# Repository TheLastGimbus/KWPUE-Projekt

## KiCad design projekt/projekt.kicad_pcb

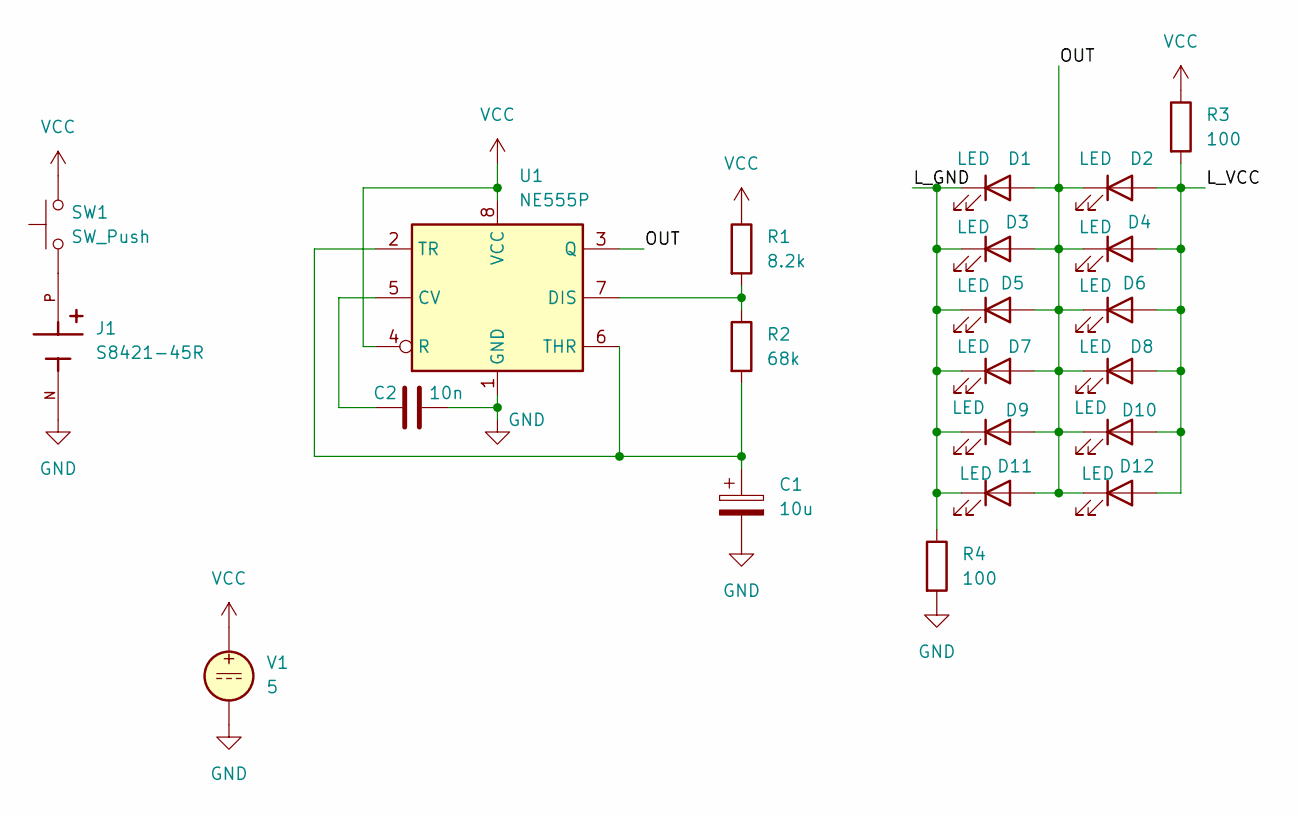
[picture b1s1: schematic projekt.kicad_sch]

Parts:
C1: 10u; CP_Radial_D4.0mm_P2.00mm
C2: 10n; C_Disc_D4.3mm_W1.9mm_P5.00mm
D1, D2, D3, D4, D5, D6, D7, D8, D9, D10, D11, D12: LED; LED_PLCC-2_3x2mm_KA
J1: S8421-45R; HARWIN_S8421-45R; PARTREV 7
R1: 8.2k; R_Axial_DIN0207_L6.3mm_D2.5mm_P7.62mm_Horizontal
R2: 68k; R_Axial_DIN0207_L6.3mm_D2.5mm_P7.62mm_Horizontal
R3, R4: 100; R_Axial_DIN0207_L6.3mm_D2.5mm_P7.62mm_Horizontal
SW1: SW_Push; SW_PUSH_6mm
U1: NE555P; DIP-8_W7.62mm
V1: 5

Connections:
/L_GND: D1.1 (K), D3.1 (K), D5.1 (K), D7.1 (K), D9.1 (K), D11.1 (K), R4.1
/L_VCC: D2.2 (A), D4.2 (A), D6.2 (A), D8.2 (A), D10.2 (A), D12.2 (A), R3.2
/OUT: D1.2 (A), D2.1 (K), D3.2 (A), D4.1 (K), D5.2 (A), D6.1 (K), D7.2 (A), D8.1 (K), D9.2 (A), D10.1 (K), D11.2 (A), D12.1 (K), U1.3 (Q)
GND: C1.2, C2.2, J1.N, R4.2, U1.1 (GND), V1.2
unnamed: J1.P, SW1.1
unnamed: C2.1, U1.5 (CV)
unnamed: R1.2, R2.1, U1.7 (DIS)
unnamed: C1.1, R2.2, U1.2 (TR), U1.6 (THR)
VCC: R1.1, R3.1, SW1.2, U1.4 (R), U1.8 (VCC), V1.1

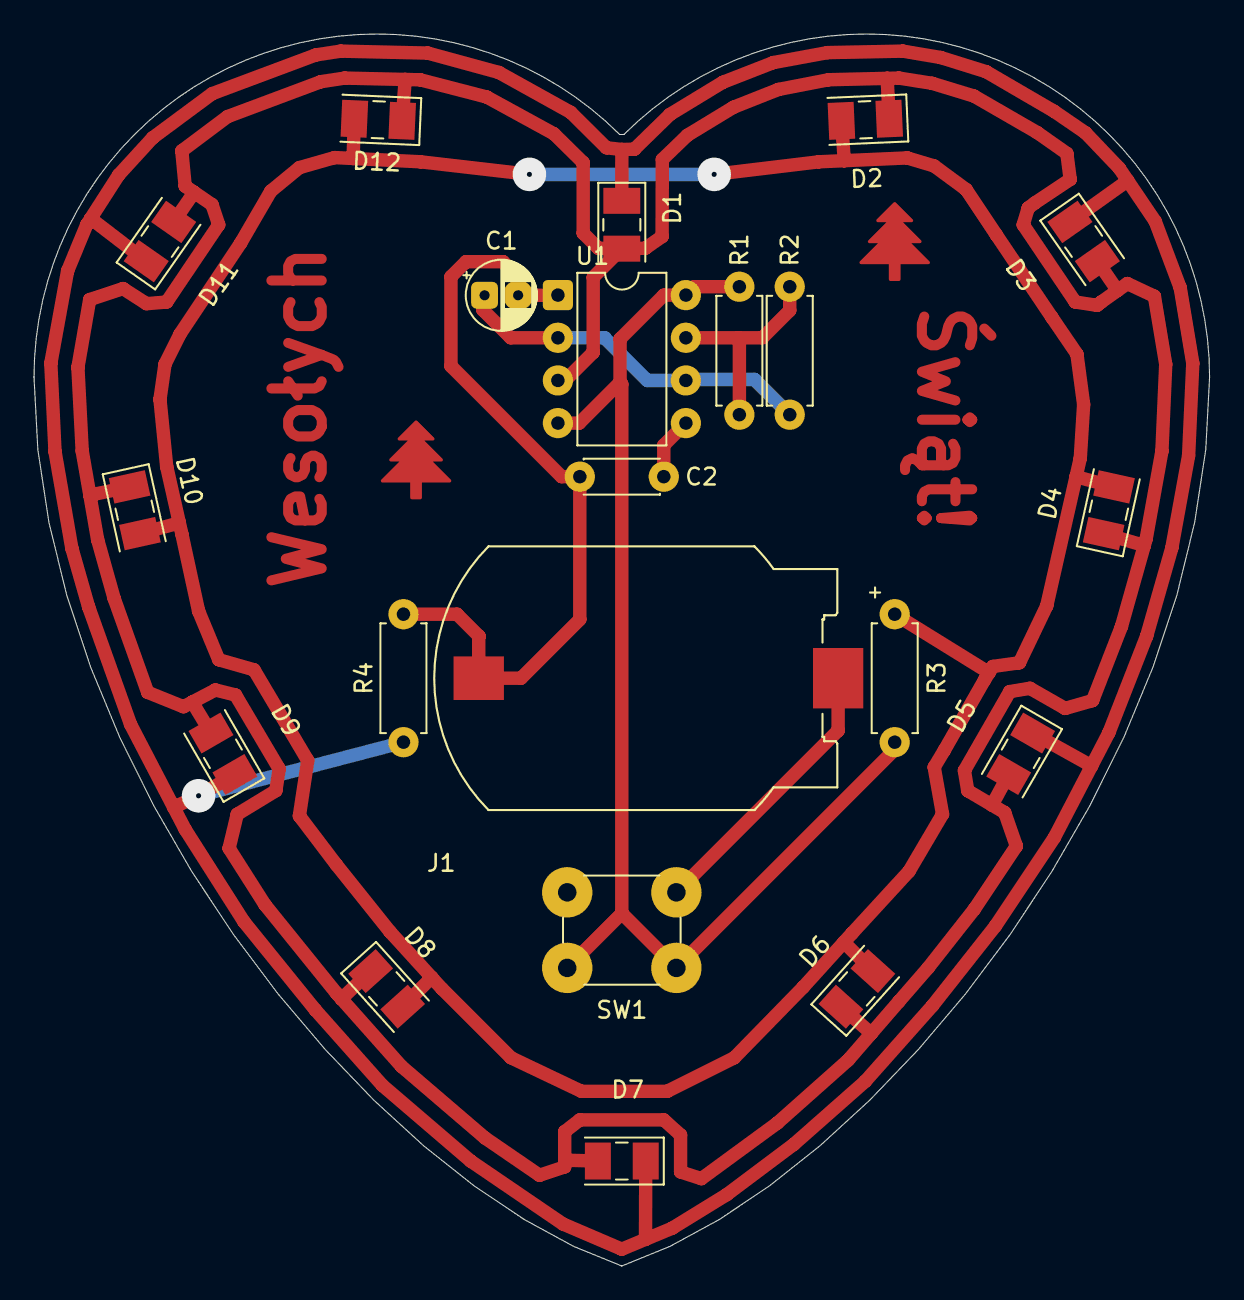
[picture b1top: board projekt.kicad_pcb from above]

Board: 2 copper layers, 70.0 x 73.4 mm, 21 parts (0 on the bottom side), 9 nets.

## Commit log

2025-12-09 ou jea
2025-12-09 cos sie zepsulo
2025-12-09 make it kinda work
2025-12-09 wow! serduszko!
2025-12-13 serduszko nawet bardziej
2025-12-13 wiekszy margines od kranca swiata
2025-12-13 pierscien
2025-12-13 ja pd udało sie - wszystkie połączenia zrobione
2025-12-13 poprawione napisy
2025-12-15 wieksze dziury
2025-12-18 V3! grubsze wszystko!
2025-12-18 forgor
2026-01-11 costam
2026-01-11 zdjęcia i wgl
2026-01-12 wszystko
2026-01-14 poczatek prezentacji i poprawka sprawka
2026-01-16 wszystko wszystko
